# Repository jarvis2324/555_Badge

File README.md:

# 555_Badge
PCB Layout of 555_Badge

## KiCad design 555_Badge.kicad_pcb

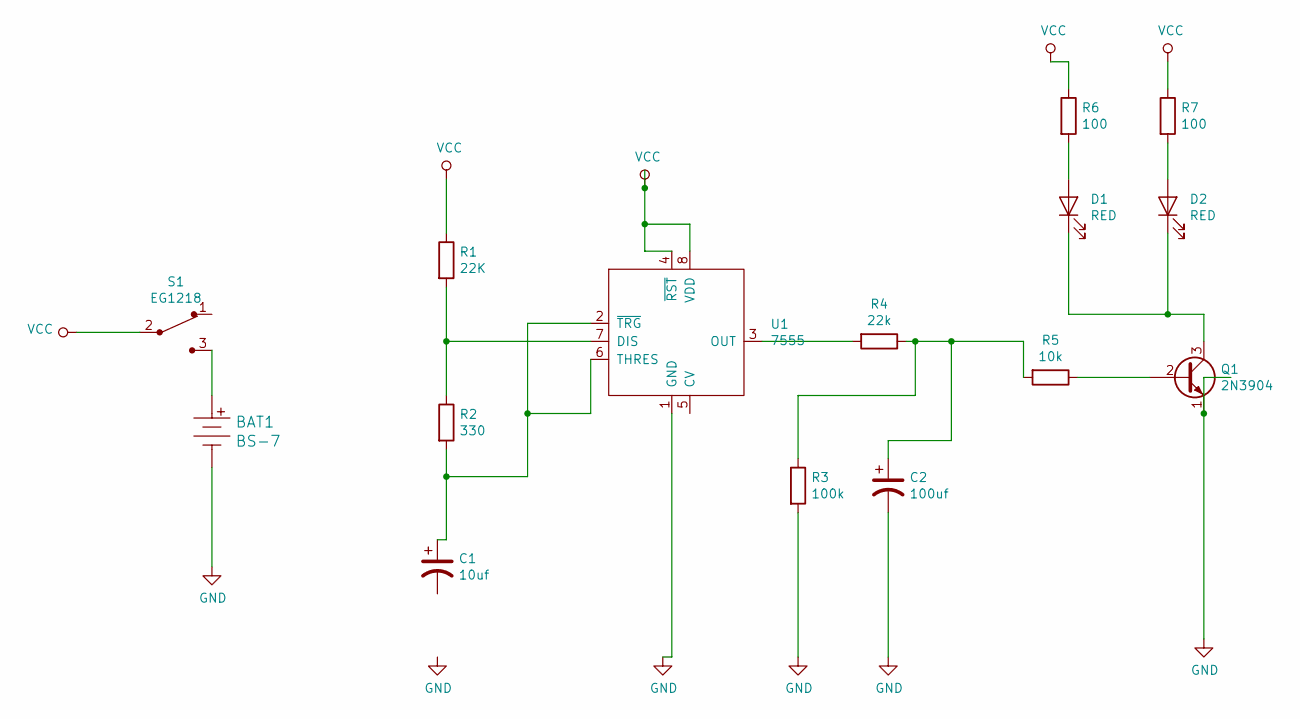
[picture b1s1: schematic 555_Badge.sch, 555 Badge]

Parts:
BAT1: BS-7; Battery_Holder_Coin_2032_BS-7; MPN BS-7; Digi-Key_PN BS-7-ND
C1: 10uf; CP_Radial_D5.0mm_P2.00mm
C2: 100uf; CP_Radial_D6.3mm_P2.50mm
D1, D2: RED; LED_D3.0mm
Q1: 2N3904; TO-92-3
R1: 22K; R_Axial_DIN0204_L3.6mm_D1.6mm_P7.62mm_Horizontal
R2: 330; R_Axial_DIN0207_L6.3mm_D2.5mm_P7.62mm_Horizontal
R3: 100k; R_Axial_DIN0207_L6.3mm_D2.5mm_P7.62mm_Horizontal
R4: 22k; R_Axial_DIN0207_L6.3mm_D2.5mm_P7.62mm_Horizontal
R5: 10k; R_Axial_DIN0207_L6.3mm_D2.5mm_P7.62mm_Horizontal
R6, R7: 100; R_Axial_DIN0207_L6.3mm_D2.5mm_P7.62mm_Horizontal
S1: EG1218; Switch_Slide_11.6x4mm_EG1218; MPN EG1218; Digi-Key_PN EG1903-ND
U1: 7555; ICM7555_PDIM

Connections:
GND: BAT1.Neg, C2.2, Q1.1 (E), R3.2, U1.1 (GND)
unnamed: BAT1.Pos, S1.3
unnamed: C1.1, R2.2, U1.2 (~TRG), U1.6 (THRES)
unnamed: C2.1, R3.1, R4.1, R5.2
unnamed: D1.1 (K), D2.1 (K), Q1.3 (C)
unnamed: D1.2 (A), R6.2
unnamed: D2.2 (A), R7.2
unnamed: Q1.2 (B), R5.1
unnamed: R1.2, R2.1, U1.7 (DIS)
unnamed: R4.2, U1.3 (OUT)
VCC: R1.1, R6.1, R7.1, S1.2, U1.4 (~RST), U1.8 (VDD)

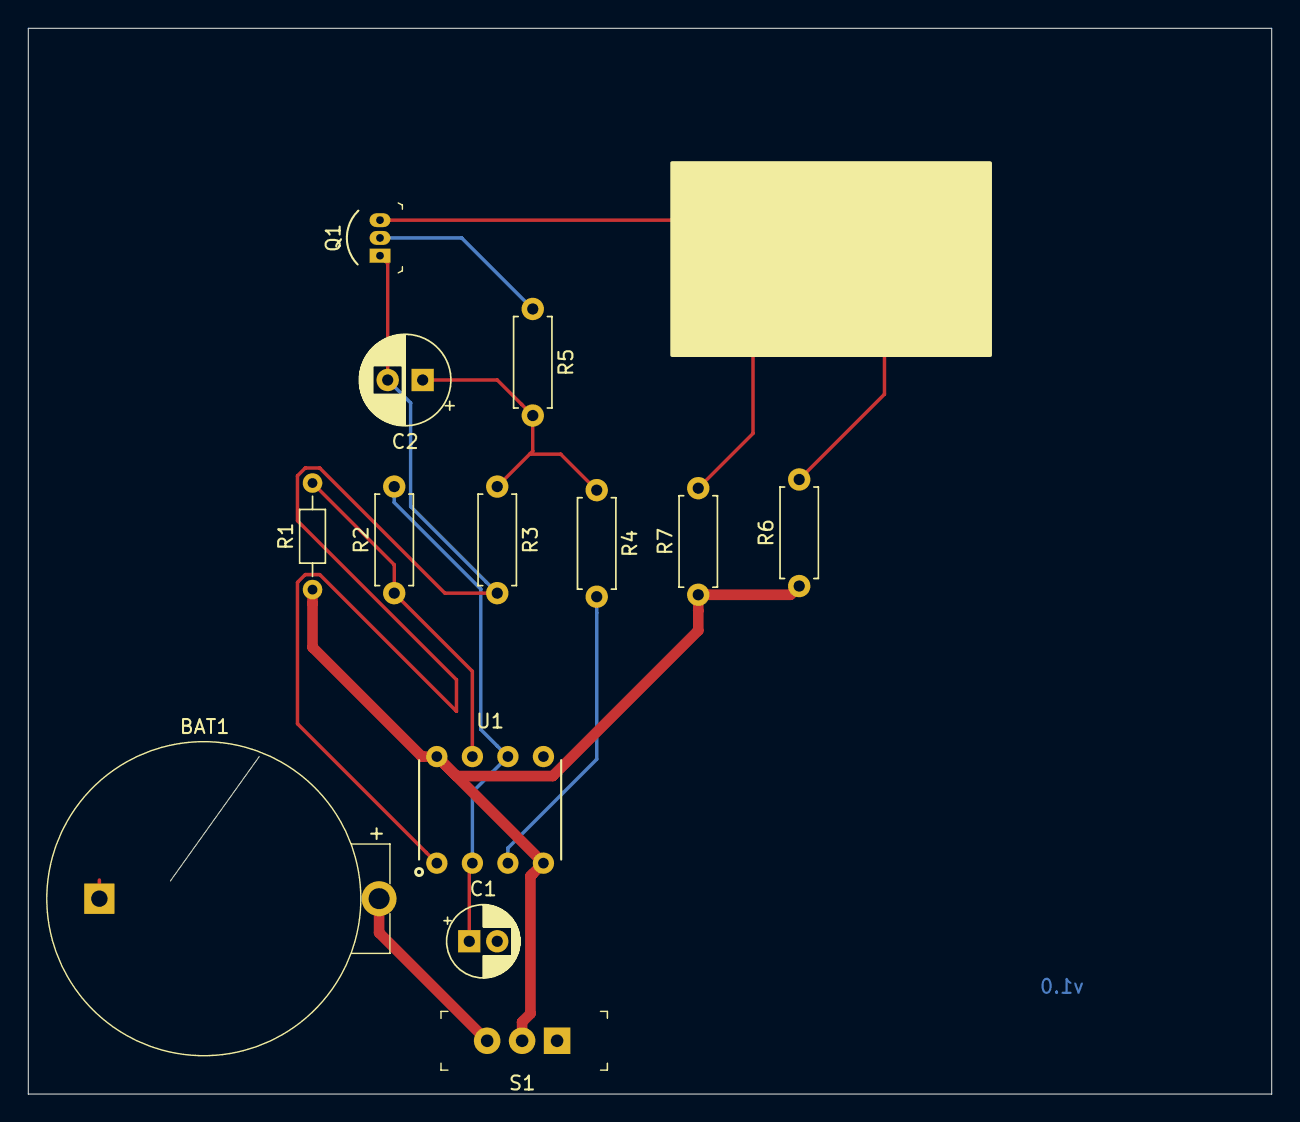
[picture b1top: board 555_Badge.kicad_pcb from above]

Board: 2 copper layers, 88.9 x 76.2 mm, 15 parts (0 on the bottom side), 11 nets.

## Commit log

2023-01-11 Created using Colaboratory
2023-02-19 Adding Comments
